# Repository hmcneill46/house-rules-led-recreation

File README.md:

# house-rules-led-recreation
Software attempt at recreating Rose Finn-Kelcey's House Rules

[Web App](https://hmcneill46.github.io/house-rules-led-recreation/)

The physical display project is documented in [hardware revision B2](hardware/revisions/B2/README.md), including editable KiCad files, firmware, printable case models, verification and prototype cost evidence. B2 uses the seven owned 5 × 7 LED modules on a hidden custom PCB, with ready-assembled controller and USB modules to reduce prototype cost.

The earlier hardware design is preserved at [hardware-a1-2026-10-29](https://github.com/hmcneill46/house-rules-led-recreation/tree/hardware-a1-2026-10-29). Read each revision's status and assembly guide before ordering or mixing files.

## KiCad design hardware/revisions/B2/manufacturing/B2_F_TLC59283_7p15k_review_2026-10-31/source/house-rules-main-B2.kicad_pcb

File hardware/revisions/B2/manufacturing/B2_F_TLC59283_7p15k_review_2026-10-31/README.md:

# House Rules B2 — MANUFACTURING REVIEW, NOT PRODUCTION APPROVAL

This package passed a fresh native KiCad10 DRC including warnings, exclusions,
unconnected items and schematic parity, after refilling/saving a staged copy.
The five ignored checks that KiCad10.0.7 uses by default are reported
explicitly; their pristine native evidence is included in reports/. UUID
exclusions, custom-rule ignores and other ignored-rule overrides are forbidden.
Its native audit checks82 references,55 factory parts,327 connected pins and the
84 LED holes against frozen A1 plus the owner-confirmed rigid module shifts
(175000nm per zero-based module index,12.875mm pitch). Individual pin patterns
and open0.90mm drill diameters stay unchanged. Separate owner-reported diode tests
verify the full12-terminal map and front orientation of ONE owned
LMD07057AUE-101B-02: part-number label on the left in the correct front view.
The other20 modules remain unverified. This does not establish powered-board
operation, actual soldered fit, USB current/compliance, brightness, thermal
performance or print fit. The owner evidence is included in reports/.
No upload, order or payment has been made by the exporter.

CURRENT DRIVER: U1..U4 = TLC59283RGER / C485815; R1..R4 =7.15k1%,
0603WAF7151T5E / C25980. Never use the historical TLC59282/6.8k BOM for
this revision. Copper, LED pitch and case geometry are preserved. Nominal
current is1.208*43.8/7.15=7.40006mA;400Hz/five phases/470us light remain.
BLANK HIGH also enables TLC59283 output precharge. Powered-off leakage and
rail transient behaviour are unspecified: both switched rails/QOD and the
clear/blank/control-low shutdown sequence remain necessary. Scope startup,
shutdown, reset/suspend and scanning; measure current, brightness uniformity,
ghosting and enclosed temperature. Static ERC/DRC cannot qualify those effects.
The owner has NOT yet completed the full case print/stock-module/plug trial.
Case fit and factory CAM/pin1 review remain pending before any order decision.

Board requirements: SIX copper layers,89.45 x17.3mm final outline,1.6mm FR4.
Layer order is F.Cu/In1.Cu/In2.Cu/In3.Cu/In4.Cu/B.Cu. In4 is GND-only. In2 is
primarily GND with one explicitly approved quiet CT_5V timing-capacitor bridge,
maximum12mm total; no other signal is allowed there. Its GND fill must remain
one connected outline. The final measured length is recorded in the audit.
In3 has signal copper including USB and GND fill; USB retains its unbroken
In4 ground reference. Confirm the actual standard dielectric
stack with the manufacturer. No controlled-impedance certification is claimed.

ALL0.30mm ordinary F-to-B plated through VIAS must be epoxy/resin FILLED and
COPPER CAPPED flat, including12 exposed-pad thermal vias (three per TLC driver)
and the selective0.45mm-pad escape vias. Most via pads are0.60mm; selected escape
pads are0.45mm, minimum annulus0.075mm. Tenting or solder plugging alone is not
equivalent to this fill/cap requirement. No blind/buried/laser vias are specified.

Actual Excellon PTH T1 =0.30mm VIA holes: FILL AND CAP ALL.
Actual Excellon PTH T2 =0.90mm LED mounting holes, exactly84: KEEP OPEN,
UNFILLED AND UNCAPPED. Never apply a blanket fill instruction to all PTH holes.
The actual drill counts and source/output hashes are in manifest.json and
reports/drill-statistics.json. There must be no other finished-board hole tools.
Both native geometry and actual Excellon holes are independently checked for
at least0.45mm via-to-LED-PTH hole-edge clearance and0.25mm via-to-via clearance,
including same-net pairs. These physical checks do not depend on copper DRC.

Narrow-board assembly may need REMOVABLE OUTSIDE RAILS and tooling chosen by the
assembler. Tooling/fiducial holes must be OUTSIDE the finished89.45x17.3mm outline,
on removable rails only. Do not add holes inside the main board or move/close the
84 LED holes. Rails must depanelise completely so the final PCB stays hidden
behind the LEDs. CAM must confirm fill/cap selection, open LED holes and final
outline tolerance before an order is approved.

Factory assembly:55 SMT components on BOTTOM ONLY. DS1..DS7 andJ1..J20 are
owner-fit modules/wire lands, excluded from every factory BOM/CPL. Their copper
and LED holes remain in Gerbers. Do not solder-fill the84 empty LED holes.
The owner supplies the XIAO RP2040 Plus and Adafruit4090 separately and wires
20 leads/40 wire-end joints; these stock modules/looms are not factory BOM parts.

ROTATION REVIEW IS REQUIRED. bom.csv uses common JLC-shaped headings; bom-review
adds exact quantities/identities. cpl-manufacturer-review.csv preserves KiCad's
native millimetre position export, same auxiliary origin as Gerbers/drill.
BOTTOM X IS NOT NEGATED. Native exported Y can be negative. No extra mirroring,
Y inversion or package-specific angle correction has been applied. Native angles
are NOT a guarantee of the manufacturer's tape/feeder/pin1 convention.
placement-review.csv adds native pad1 coordinates relative to the auxiliary
origin, using native board XY (distinct from exported CPL Y), BOTTOM side,
exact MPN/LCSC, native angle and uncorrected CPL rotation. Review
all asymmetric components in the assembler's placement preview, especially QFNs,
PMOS switches, load switches, ESD/BC chips and diode polarity. Obtain the factory's
concrete placement/process review before production. No silent substitutions.

fabrication/ contains six actual Gerber X2 copper layers, both masks/silks, outline,
metric Excellon PTH/NPTH, drill map and Gerber job metadata. Its ZIP contains
fabrication files only. assembly/ adds paste Gerbers and factory CSVs. reports/
contains native DRC, exact board audit and actual drill statistics. source/ retains
the exact refilled/saved board used for these outputs plus project/schematic/rules
and local footprint libraries. source/3d/ includes the bundled model assets.
Every model referenced by the actual staged PCB must resolve through
${KIPRJMOD}/3d/ inside this snapshot; installed/global model fallbacks, absolute
paths and escaping relative paths are rejected. reports/3d-model-portability.json
records each reference/hash and explicitly lists footprints lacking a 3D model.
Absent models are not a claim of absent physical components. The repository
also retains generators, mechanical design, firmware and earlier source history.
The source canonical PCB was not modified. manifest.json links all inputs and
outputs to SHA256 hashes; a later change requires a fresh audit/export/quote.

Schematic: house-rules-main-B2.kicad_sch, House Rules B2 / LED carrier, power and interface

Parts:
C1, C2, C3, C4, C15: 100n 50V X7R; C_0603_1608Metric; MPN CC0603KRX7R9BB104; LCSC C14663
C5, C6, C7, C14, C16: 1u 50V X5R; C_0603_1608Metric; MPN CL10A105KB8NNNC; LCSC C15849
C8: 4u7 16V X5R; C_0603_1608Metric; MPN CL10A475KO8NNNC; LCSC C19666
C9, C10, C13: 1n 50V X7R; C_0603_1608Metric; MPN CL10B102KB8NNNC; LCSC C1588
C11, C12: 10n 50V X7R; C_0603_1608Metric; MPN 0603B103K500NT; LCSC C57112
D1: SMF5.0A; D_SOD-123F; MPN SMF5.0A; LCSC C151296
DS1, DS2, DS3, DS4, DS5, DS6, DS7: LMD07057AUE-101B; MPN LMD07057AUE-101B
F1: 750mA PPTC; Fuse_1206_3216Metric; MPN SMD1206B075TF/16; LCSC C269118
J1: +5V; WirePad_B2; MPN +5V
J2, J14: GND; WirePad_B2; MPN GND
J3: +3V3; WirePad_B2; MPN +3V3
J4: SIN; WirePad_B2; MPN SIN
J5: SCLK; WirePad_B2; MPN SCLK
J6: LAT; WirePad_B2; MPN LAT
J7: BLANK; WirePad_B2; MPN BLANK
J8: DRIVER_EN; WirePad_B2; MPN DRIVER_EN
J9: CC1_ADC; WirePad_B2; MPN CC1_ADC
J10: CC2_ADC; WirePad_B2; MPN CC2_ADC
J11: USB_DM_HOST; WirePad_B2; MPN USB_DM_HOST
J12: USB_DP_HOST; WirePad_B2; MPN USB_DP_HOST
J13: VBUS; WirePad_B2; MPN VBUS
J15: CC1; WirePad_B2; MPN CC1
J16: CC2; WirePad_B2; MPN CC2
J17: USB_DM; WirePad_B2; MPN USB_DM
J18: USB_DP; WirePad_B2; MPN USB_DP
J19: BC_DET; WirePad_B2; MPN BC_DET
J20: BC_AL_N; WirePad_B2; MPN BC_AL_N
Q1, Q2, Q3, Q4, Q5: AO3401A; SOT-23; MPN AO3401A; LCSC C15127
R1, R2, R3, R4: 7k15 1%; R_0603_1608Metric; MPN 0603WAF7151T5E; LCSC C25980
R5, R6, R7, R8, R9, R15: 4k7 1%; R_0603_1608Metric; MPN 0603WAF4701T5E; LCSC C23162
R10, R11, R12, R13, R14, R21, R23: 10k 1%; R_0603_1608Metric; MPN 0603WAF1002T5E; LCSC C25804
R16: 100k 1%; R_0603_1608Metric; MPN 0603WAF1003T5E; LCSC C25803
R17, R18, R19, R20: 47k 1%; R_0603_1608Metric; MPN 0603WAF4702T5E; LCSC C25819
R22: 15k 1%; R_0603_1608Metric; MPN 0603WAF1502T5E; LCSC C22809
U1, U2, U3, U4: TLC59283RGER; RGE0024C; MPN TLC59283RGER; LCSC C485815
U5, U6, U8: TPS22918DBVR; SOT-23-6; MPN TPS22918DBVR; LCSC C131941
U7: TPD4E05U06DQAR; USON-10_2.5x1.0mm_P0.5mm; MPN TPD4E05U06DQAR; LCSC C138714
U9: BQ24392RSER; Texas_UQFN-10_1.5x2mm_P0.5mm; MPN BQ24392RSER; LCSC C128408

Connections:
+3V3: C5.1, J3.1, R23.2, U5.1 (VIN), U9.5 (GOOD_BAT)
+5V: C6.1, C15.1, C16.1, J1.1, U6.1 (VIN), U8.5 (QOD), U8.6 (VOUT), U9.9 (VBUS)
BC_AL_N: J20.1, R23.1, U9.4 (CHG_AL_N)
BC_DET: J19.1, R21.2, R22.1
BC_DET_5V: R21.1, U9.10 (CHG_DET)
BLANK: J7.1, R15.1, U1.18 (BLANK), U2.18 (BLANK), U3.18 (BLANK), U4.18 (BLANK)
CC1: J15.1, R17.1, U7.4, U7.7
CC1_ADC: C11.1, J9.1, R17.2, R18.1
CC2: J16.1, R19.1, U7.5, U7.6
CC2_ADC: C12.1, J10.1, R19.2, R20.1
COL1_A: DS1.1, DS2.1, DS3.1, DS4.1, DS5.1, DS6.1, DS7.1, Q1.3 (D), R10.1
COL1_GATE: Q1.1 (G), R5.1, U4.9 (OUT7)
COL2_A: DS1.3, DS2.3, DS3.3, DS4.3, DS5.3, DS6.3, DS7.3, Q2.3 (D), R11.1
COL2_GATE: Q2.1 (G), R6.1, U4.10 (OUT8)
COL3_A: DS1.10, DS2.10, DS3.10, DS4.10, DS5.10, DS6.10, DS7.10, Q3.3 (D), R12.1
COL3_GATE: Q3.1 (G), R7.1, U4.11 (OUT9)
COL4_A: DS1.7, DS2.7, DS3.7, DS4.7, DS5.7, DS6.7, DS7.7, Q4.3 (D), R13.1
COL4_GATE: Q4.1 (G), R8.1, U4.12 (OUT10)
COL5_A: DS1.8, DS2.8, DS3.8, DS4.8, DS5.8, DS6.8, DS7.8, Q5.3 (D), R14.1
COL5_GATE: Q5.1 (G), R9.1, U4.13 (OUT11)
CT_3V3: C9.1, U5.4 (CT)
CT_5V: C10.1, U6.4 (CT)
CT_INPUT: C13.1, U8.4 (CT)
D1_ROW1_K: DS1.12, U1.2 (OUT0)
D1_ROW2_K: DS1.11, U1.3 (OUT1)
D1_ROW3_K: DS1.2, U1.4 (OUT2)
D1_ROW4_K: DS1.9, U1.5 (OUT3)
D1_ROW5_K: DS1.4, U1.6 (OUT4)
D1_ROW6_K: DS1.5, U1.7 (OUT5)
D1_ROW7_K: DS1.6, U1.8 (OUT6)
D1_ROW8_K: DS2.12, U1.9 (OUT7)
D1_ROW9_K: DS2.11, U1.10 (OUT8)
D1_ROW10_K: DS2.2, U1.11 (OUT9)
D1_ROW11_K: DS2.9, U1.12 (OUT10)
D1_ROW12_K: DS2.4, U1.13 (OUT11)
D1_ROW13_K: DS2.5, U1.14 (OUT12)
D1_ROW14_K: DS2.6, U1.15 (OUT13)
D2_ROW1_K: DS3.12, U2.2 (OUT0)
D2_ROW2_K: DS3.11, U2.3 (OUT1)
D2_ROW3_K: DS3.2, U2.4 (OUT2)
D2_ROW4_K: DS3.9, U2.5 (OUT3)
D2_ROW5_K: DS3.4, U2.6 (OUT4)
D2_ROW6_K: DS3.5, U2.7 (OUT5)
D2_ROW7_K: DS3.6, U2.8 (OUT6)
D2_ROW8_K: DS4.12, U2.9 (OUT7)
D2_ROW9_K: DS4.11, U2.10 (OUT8)
D2_ROW10_K: DS4.2, U2.11 (OUT9)
D2_ROW11_K: DS4.9, U2.12 (OUT10)
D2_ROW12_K: DS4.4, U2.13 (OUT11)
D2_ROW13_K: DS4.5, U2.14 (OUT12)
D2_ROW14_K: DS4.6, U2.15 (OUT13)
D3_ROW1_K: DS5.12, U3.2 (OUT0)
D3_ROW2_K: DS5.11, U3.3 (OUT1)
D3_ROW3_K: DS5.2, U3.4 (OUT2)
D3_ROW4_K: DS5.9, U3.5 (OUT3)
D3_ROW5_K: DS5.4, U3.6 (OUT4)
D3_ROW6_K: DS5.5, U3.7 (OUT5)
D3_ROW7_K: DS5.6, U3.8 (OUT6)
D3_ROW8_K: DS6.12, U3.9 (OUT7)
D3_ROW9_K: DS6.11, U3.10 (OUT8)
D3_ROW10_K: DS6.2, U3.11 (OUT9)
D3_ROW11_K: DS6.9, U3.12 (OUT10)
D3_ROW12_K: DS6.4, U3.13 (OUT11)
D3_ROW13_K: DS6.5, U3.14 (OUT12)
D3_ROW14_K: DS6.6, U3.15 (OUT13)
D4_ROW1_K: DS7.12, U4.2 (OUT0)
D4_ROW2_K: DS7.11, U4.3 (OUT1)
D4_ROW3_K: DS7.2, U4.4 (OUT2)
D4_ROW4_K: DS7.9, U4.5 (OUT3)
D4_ROW5_K: DS7.4, U4.6 (OUT4)
D4_ROW6_K: DS7.5, U4.7 (OUT5)
D4_ROW7_K: DS7.6, U4.8 (OUT6)
DRIVER_EN: J8.1, R16.1, U5.3 (ON), U6.3 (ON)
FUSED_VBUS: C14.1, F1.2, U8.1 (VIN), U8.3 (ON)
GND: C1.2, C2.2, C3.2, C4.2, C5.2, C6.2, C7.2, C8.2, C9.2, C10.2, C11.2, C12.2, C13.2, C14.2, C15.2, C16.2, D1.2, J2.1, J14.1, R1.2, R2.2, R3.2, R4.2, R10.2, R11.2, R12.2, R13.2, R14.2, R16.2, R18.2, R20.2, R22.2, U1.22 (GND), U1.25 (EP_GND), U2.22 (GND), U2.25 (EP_GND), U3.22 (GND), U3.25 (EP_GND), U4.22 (GND), U4.25 (EP_GND), U5.2 (GND), U6.2 (GND), U7.3, U7.8, U8.2 (GND), U9.6 (GND)
IREF1: R1.1, U1.20 (IREF)
IREF2: R2.1, U2.20 (IREF)
IREF3: R3.1, U3.20 (IREF)
IREF4: R4.1, U4.20 (IREF)
LAT: J6.1, U1.1 (LAT), U2.1 (LAT), U3.1 (LAT), U4.1 (LAT)
SCLK: J5.1, U1.24 (SCLK), U2.24 (SCLK), U3.24 (SCLK), U4.24 (SCLK)
SERIAL_1_2: U1.19 (SOUT), U2.23 (SIN)
SERIAL_2_3: U2.19 (SOUT), U3.23 (SIN)
SERIAL_3_4: U3.19 (SOUT), U4.23 (SIN)
SIN: J4.1, U1.23 (SIN)
SW_3V3: C1.1, C2.1, C3.1, C4.1, C7.1, R15.2, U1.21 (VCC), U2.21 (VCC), U3.21 (VCC), U4.21 (VCC), U5.5 (QOD), U5.6 (VOUT)
USB_DM: J17.1, U7.1, U7.10, U9.8 (DM_CON)
USB_DM_HOST: J11.1, U9.2 (DM_HOST)
USB_DP: J18.1, U7.2, U7.9, U9.7 (DP_CON)
USB_DP_HOST: J12.1, U9.3 (DP_HOST)
VBUS: D1.1, F1.1, J13.1
VLED_5V: C8.1, Q1.2 (S), Q2.2 (S), Q3.2 (S), Q4.2 (S), Q5.2 (S), R5.2, R6.2, R7.2, R8.2, R9.2, U6.5 (QOD), U6.6 (VOUT)

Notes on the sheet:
BANK1 / DS1 + DS2
BANK2 / DS3 + DS4
BANK3 / DS5 + DS6
BANK4 / DS7 and gate sinks / USB INPUT SOFT START
COLUMN1..3 / gate pullups and anode discharge
COLUMN4..5 / gate pullups and anode discharge
RAIL SWITCHES / common EN / quick discharge
USB / CC current sensing and ESD
BC1.2 / automatic USB switch / GOOD_BAT uses always3V3
MCU WIRES J1..J10 / external XIAO RP2040 Plus
MCU DATA / BC STATUS + USB BREAKOUT WIRES / do not power both USB sockets
Named labels connect matching nodes. Every package pin is explicit; crosses mark intentional no-connects. Owner-supplied LEDs and wire pads are excluded from factory assembly.
TLC59283RGER + IREF=7.15k: 7.40006mA nominal. U4 OUT7..11 sink PMOS gates, exactly one selected column. BLANK HIGH disables sinks and enables precharge.
400Hz frame / 5x500us phases / >=30us BLANK before next phase / <=470us full on. LAT LOW while shifting, pulse HIGH then LOW while blanked.
USB-C 5V only, no PD. Adafruit4090 supplies separate5.1k Rd resistors; no duplicate Rd on this board. CC divider loading checked against tolerance.
Both TPS22918 switches default OFF. BLANK pullup uses SW_3V3. Park serial controls LOW and BLANK high-Z before disabling rails to prevent backfeed.
TPD4E05U06 opposite NC pads are joined by external copper to corresponding DC nets. Do not treat the IC as internally flow-through.
BQ24392 isolates raw USB_DP/DM from USB_DP_HOST/DM_HOST. GOOD_BAT always3V3; BC full grant requires DET HIGH and AL_N LOW; host suspend always overrides.
One owned LED diode-verified; check other20. Full case print pending. Precharge/rail transients/current/inrush/suspend, 30us settling and temperature need bench tests. In2: CT_5V<=12mm only; In4: pure GND.

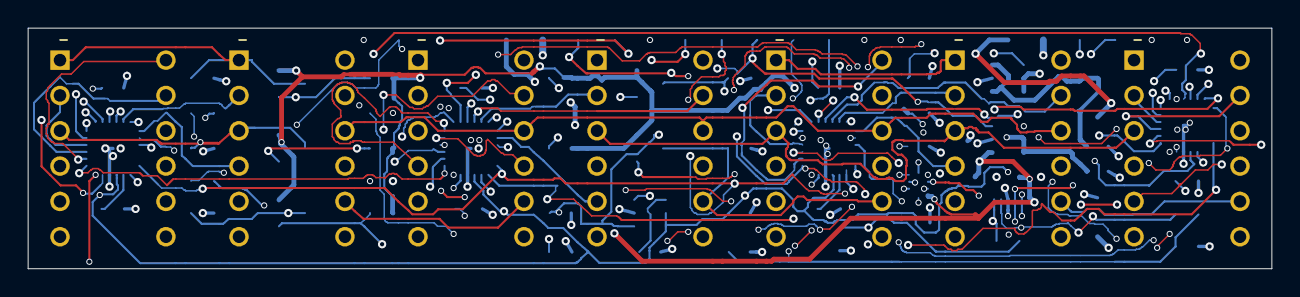
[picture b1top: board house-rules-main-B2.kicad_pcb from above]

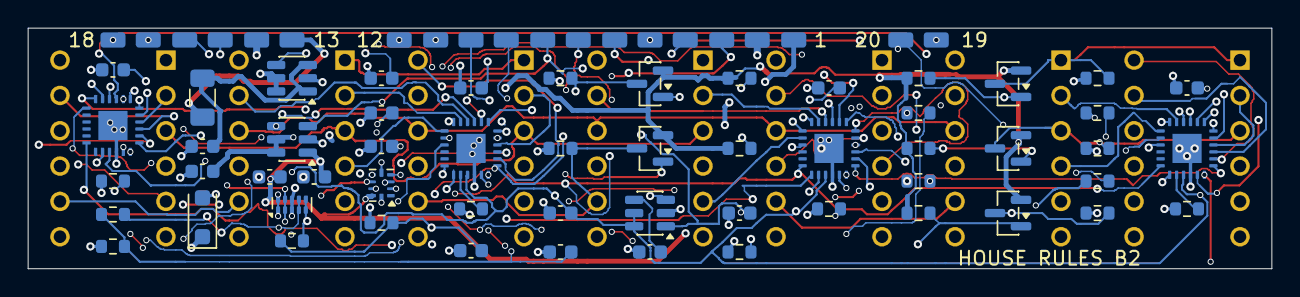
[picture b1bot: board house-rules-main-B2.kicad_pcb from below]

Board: 6 copper layers, 89.4 x 17.3 mm, 82 parts (75 on the bottom side), 92 nets.

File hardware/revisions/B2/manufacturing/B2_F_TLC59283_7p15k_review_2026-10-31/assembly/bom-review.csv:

MPN,LCSC,Qty,Designators,Value,Footprint
0603B103K500NT,C57112,2,"C11,C12",10n 50V X7R,Capacitor_SMD:C_0603_1608Metric
0603WAF1002T5E,C25804,7,"R10,R11,R12,R13,R14,R21,R23",10k 1%,Resistor_SMD:R_0603_1608Metric
0603WAF1003T5E,C25803,1,R16,100k 1%,Resistor_SMD:R_0603_1608Metric
0603WAF1502T5E,C22809,1,R22,15k 1%,Resistor_SMD:R_0603_1608Metric
0603WAF4701T5E,C23162,6,"R5,R6,R7,R8,R9,R15",4k7 1%,Resistor_SMD:R_0603_1608Metric
0603WAF4702T5E,C25819,4,"R17,R18,R19,R20",47k 1%,Resistor_SMD:R_0603_1608Metric
0603WAF7151T5E,C25980,4,"R1,R2,R3,R4",7k15 1%,Resistor_SMD:R_0603_1608Metric
AO3401A,C15127,5,"Q1,Q2,Q3,Q4,Q5",AO3401A,Package_TO_SOT_SMD:SOT-23
BQ24392RSER,C128408,1,U9,BQ24392RSER,Package_DFN_QFN:Texas_UQFN-10_1.5x2mm_P0.5mm
CC0603KRX7R9BB104,C14663,5,"C1,C2,C3,C4,C15",100n 50V X7R,Capacitor_SMD:C_0603_1608Metric
CL10A105KB8NNNC,C15849,5,"C5,C6,C7,C14,C16",1u 50V X5R,Capacitor_SMD:C_0603_1608Metric
CL10A475KO8NNNC,C19666,1,C8,4u7 16V X5R,Capacitor_SMD:C_0603_1608Metric
CL10B102KB8NNNC,C1588,3,"C9,C10,C13",1n 50V X7R,Capacitor_SMD:C_0603_1608Metric
SMD1206B075TF/16,C269118,1,F1,750mA PPTC,Fuse:Fuse_1206_3216Metric
SMF5.0A,C151296,1,D1,SMF5.0A,Diode_SMD:D_SOD-123F
TLC59283RGER,C485815,4,"U1,U2,U3,U4",TLC59283RGER,TI:RGE0024C
TPD4E05U06DQAR,C138714,1,U7,TPD4E05U06DQAR,Package_SON:USON-10_2.5x1.0mm_P0.5mm
TPS22918DBVR,C131941,3,"U5,U6,U8",TPS22918DBVR,Package_TO_SOT_SMD:SOT-23-6

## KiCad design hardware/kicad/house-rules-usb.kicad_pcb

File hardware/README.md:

# Physical House Rules — prototype A1

**Historical A1 design.** The current build is [revision B2](revisions/B2/README.md), updated on 31 October to the owner's confirmed 12.875 mm module pitch and 89.45 mm PCB width. The earlier 12.70 mm fit assumption and files below are superseded for new builds. They remain here as design history.

A complete editable electronics design for seven owner-supplied Wenrun LMD07057AUE-101B displays, arranged as a **35 × 7, 245-dot** screen. Designed 29 October 2026. This is a **prototype awaiting physical validation**, with fabrication and assembly files for review. No boards have been ordered or tested. Start with [the illustrated summary](design-summary.html).

## What was designed

| Item | Design |
| --- | --- |
| Display arrangement | Seven upright modules, 12.70 mm centre spacing; user reports seven-module printed-fixture fit passed |
| Main PCB | 88.4 × 17.3 × 1.6 mm, six copper layers |
| USB carrier | 16.0 × 16.8 × 1.0 mm, four copper layers, behind right end |
| Drivers | Four IS31FL3729-QFLS4-TR, addressing 2 + 2 + 2 + 1 modules |
| Controller | STM32G0B1KBU6, 128 KB flash, native USB and factory DFU |
| Factory assembly | 37 main-board SMD placements on B; seven carrier placements on F |
| Owner assembly | Seven LED modules: 84 through-hole joints per unit; plug-in six-wire harness |
| Power | USB 5 V only; both A-to-C and C-to-C cables |
| Enclosure concept | 93.6 × 22.6 × 24 mm, printable shell and removable rear carrier cradle |

The PCB is inset 0.25 mm from the **nominal** 88.9 × 17.8 mm seven-module envelope. On 29 October 2026 the owner reported that the printed pin-fit plate worked and all seven LED modules fitted very nicely. The plate shares the main PCB's 88.4 × 17.3 mm outline and 84 pin centres. Its 1.0 mm thickness and nominal 1.0 mm holes differ from the main PCB's 1.6 mm thickness and 0.9 mm finished holes. This confirms the reported group's mechanical arrangement, while electrical orientation, actual PCB hole tolerances and the other two groups remain separate checks. See [the recorded user fit result](reports/user-fit-confirmation-2026-10-29.json).

The USB carrier solves a physical conflict: the selected USB socket will not fit directly between the LED solder leads. It remains within the display's projected outline and connects through a short keyed JST-SH six-way harness, with a vertical header on the main board to clear the LED lead stubs. The bottom-right socket sits approximately **1.825 mm recessed** behind the concept case's outer wall, with a 14 × 6.5 mm plug well. A cable plug protrudes. The case is an editable fit concept; verify the chosen plug and actual assembly before printing a final shell.

## Where to look

- [Main KiCad project](kicad/house-rules-main.kicad_pro), [main PCB](kicad/house-rules-main.kicad_pcb), [schematic](kicad/house-rules-main.kicad_sch).
- [USB KiCad project](kicad/house-rules-usb.kicad_pro), [carrier PCB](kicad/house-rules-usb.kicad_pcb), [schematic](kicad/house-rules-usb.kicad_sch).
- [Native CAD renders](render/), including front with LEDs, bare front, component rear and carrier views.
- Manufacturing review output: `manufacturing/A1_review/`, generated after final CAD checks. It contains separate Gerber/drill archives, exact-part BOM and placement files for each board. The illustrated summary links it once exported; it is a review package, not an instruction to order immediately.
- [Offline pin-level simulator](simulation/matrix-emulator.html), [model scope](simulation/README.md).
- [Compiled firmware and programming guide](firmware/README.md), [BIN](firmware/compiled/HouseRules.ino.bin), [ELF](firmware/compiled/HouseRules.ino.elf).
- [1:1 pin-fit template](mechanical/pin-fit-template.svg), [soldering alignment tray](mechanical/README.md), [case and assembly stack](mechanical/enclosure-notes.md).
- [Assembly and test instructions](assembly-and-test.md), [verification reports](reports/).

## Electronics and brightness

These are raw LED matrices, with no controller or current limiting inside. The [Wenrun datasheet](https://cdn.shopify.com/s/files/1/0695/1347/8453/files/LMD07057AUE.pdf) specifies column anodes 1, 3, 10, 7, 8 (left to right) and row cathodes 12, 11, 2, 9, 4, 5, 6 (top to bottom). The custom footprint numbers the front-view left strip 1–6 downward and the right strip 12–7 downward. A physical single-pixel check is still required: the photos identify a -101B-Q2 suffix whose meaning is not established. Never connect a module directly across 5 V.

Each driver selects five shared anode columns and supplies independent current sinks to each module's seven rows. The paired modules share anodes only; their cathodes remain independent. Addresses are 0x34–0x37. Four 47 kohm, 1% ISET resistors limit nominal full-scale dot current to approximately **7.25 mA peak**, below the LED's 20 mA continuous absolute maximum. The 80 mA pulse rating is conditional on duty ≤1/10 and is **not applicable** to the selected five-phase scan. No separate resistor is needed for every dot because the drivers regulate current.

The calculated all-on LED load is approximately **342 mA average**, before MCU and driver overhead. The default dim mode uses approximately 43 mA average LED current. These are nominal calculations, not measured input current or guaranteed brightness. Compare brightness and timing with the reference and measure full-on temperature/current before considering any increase. Driver register details and source references are in [the functional model](simulation/README.md); local manufacturer PDFs are in [reference/](reference/).

The six-layer main board reserves In1 for GND and In4 for +5 V; F/In2/In3/B carry signals. The USB data pair follows the front copper's upper margin, with the adjacent GND layer providing its reference. Default copper clearance is 0.15 mm. A documented 0.10 mm via-to-pad rule applies only inside each LED driver courtyard, enabling filled/capped QFN fanout; via-to-track and via-to-via spacing retain the default. All vias are intended as ordinary full-stack through vias, with minimum 0.4 mm copper / 0.2 mm drill. There is no blind-via or HDI requirement. The design does not claim controlled 90-ohm impedance or USB certification; the short harness and entire USB path require hardware tests.

## USB and programming

Separate 5.1 kohm CC resistors make the board a 5 V USB-C sink in either plug orientation. No high-voltage Power Delivery negotiation is needed. The input has a resettable fuse, a 5 V TVS and data/CC ESD protection. Independent 47k/47k dividers let the MCU conservatively detect Type-C current advertisements without violating CC termination or ADC input-impedance limits.

Firmware starts with drivers disabled, performs source qualification, and uses full brightness only after a configured 500 mA USB connection, a positively identified BC1.2 charging port, or a conservative sufficient Type-C current indication. Unknown/default-current sources run dim; host suspend blanks and enters a low-power path. Inrush, total input/suspend current, BC1.2 detection and wake still require bench measurements. A fuse does not grant permission to draw current.

Use a **USB data cable** and STM32CubeProgrammer to load the factory USB DFU bootloader. A virgin blank MCU normally enters ROM automatically. After first programming, set and verify the documented G0B1 boot option bytes so holding BOOT while resetting re-enters DFU. Five SWD recovery pads remain accessible with the rear cover removed. BOOT shares PA14/SWCLK on this exact part. Follow [the exact programming steps](firmware/README.md); the running USB serial interface is not itself a flashing bootloader.

## Software checks and their limits

Native KiCad ERC, schematic-netlist comparison and PCB DRC/parity reports are saved in `reports/`. Check their current timestamps and counts; the illustrated summary reads the reports rather than assuming success. ERC/DRC establish represented connectivity and geometric rules, not physical LED identification, analogue behaviour or manufacturing yield.

The offline model reconstructs the display by traversing independently defined LED diode terminals and the actual module-to-driver connections. All 245 walking pixels and the artwork's 22,248 distinct windows were checked. Twenty-six host tests pass, including deliberate row/polarity/shared-cathode faults; see the timestamped [software verification record](reports/software-verification.json). A separately compiled C++ playback test compares **60,000 frames and two complete traversals** with the original recreation. The compiled ARM image occupies 66,108 bytes flash and 4,560 bytes static RAM. Its USB descriptor and critical startup/power hooks were inspected in the ELF. These checks do not execute the MCU or establish physical USB compliance.

## Manufacture and minimise repeat costs

Quote **three main boards and three carriers**, with the small components assembled and the 21 existing modules retained locally. Also compare a minimum pilot assembly quantity before committing all three. Fit and prove one unit before soldering the remaining 14 displays; a single assembly batch may avoid paying two sets of setup and UK shipping again. Use the full-size paper template and soldering jig first to reduce mechanical risk.

First supplier to quote is [JLCPCB Economic PCBA](https://jlcpcb.com/capabilities/pcb-assembly-capabilities): its published capabilities support these board dimensions, single-side assembly, 0.4 mm QFN pitch, 0402 parts and 2/4/6-layer boards. Main assembly is on B; carrier assembly is on F. The main BOOT switch has a 2.2 kohm series resistor so it can safely share PA14 with the SWD clock. Request green FR-4, 1 oz copper, standard six-layer 1.6 mm main stack and four-layer 1.0 mm carrier stack. Have the factory review QFN stencil/thermal vias and choose filled/capped treatment for exposed-pad vias; do not assume mask tenting will seal them. Confirm 0.2 mm drill/0.4 mm via pricing and exact part stock before paying. The manufacturer must check placement rotations and polarity in its assembly viewer.

[PCBWay assembly](https://www.pcbway.com/pcb-assembly.html) is a useful competing total-delivered quote. Bare boards alone are poor value if the tiny QFNs then need a separate assembler. No live project quote has been obtained; an earlier rough £40–90 allowance predated the final two-board, six-layer design and must not be treated as a price. Compare fabrication, two assembly setups, component/feeder fees, short harnesses, shipping and UK VAT together. The package contains exact MPN/LCSC fields and a sourcing review; stock snapshots are not reservations. Nothing has been purchased or uploaded to a manufacturer.

Before order: verify seven-module fit and pin orientation, review the Gerbers and assembly rotations, obtain the actual quote, and agree the thermal-via/stencil process. After delivery: inspect and test the empty electronics, program via USB, fit one LED and run diagnostics, then finish the first unit and measure it. Only after that should the other units be populated. A PCB electrical test cannot prove the animation or LED polarity.

## Tools and reproducibility

KiCad 10.0.7, Freerouting 2.5.0 and pinned Arduino tooling were installed locally. KiCad provides the editable schematic/PCB, native rule checks, manufacturing exports and faithful 3D images. [atopile](https://github.com/atopile/atopile) and [tscircuit](https://tscircuit.com/) are viable code-first tools; native KiCad was selected here for the custom footprint, tight mechanical layout and review/export workflow. Python-generated circuit data retains a code-readable source alongside the native files. No matching PCB MCP plugin was found in the available directory; no unofficial server was required.

`tools/circuit_spec.py` is the electrical/placement specification. `build_schematics.py --verify` rebuilds schematics and verifies their nets. **`build_pcbs.py` recreates placement and discards routing**; do not run it over a final routed board casually. Recorded `.dsn`/`.ses` files are routing intermediates, and the final native `.kicad_pcb` files include manual finishing work. `finalize_pcbs.py --metadata-only` refreshes fields without importing an old session. Preserve the final native boards as the deliverables. See [tool versions](design/tooling.txt) and [third-party library notices](kicad/third-party/README.md).

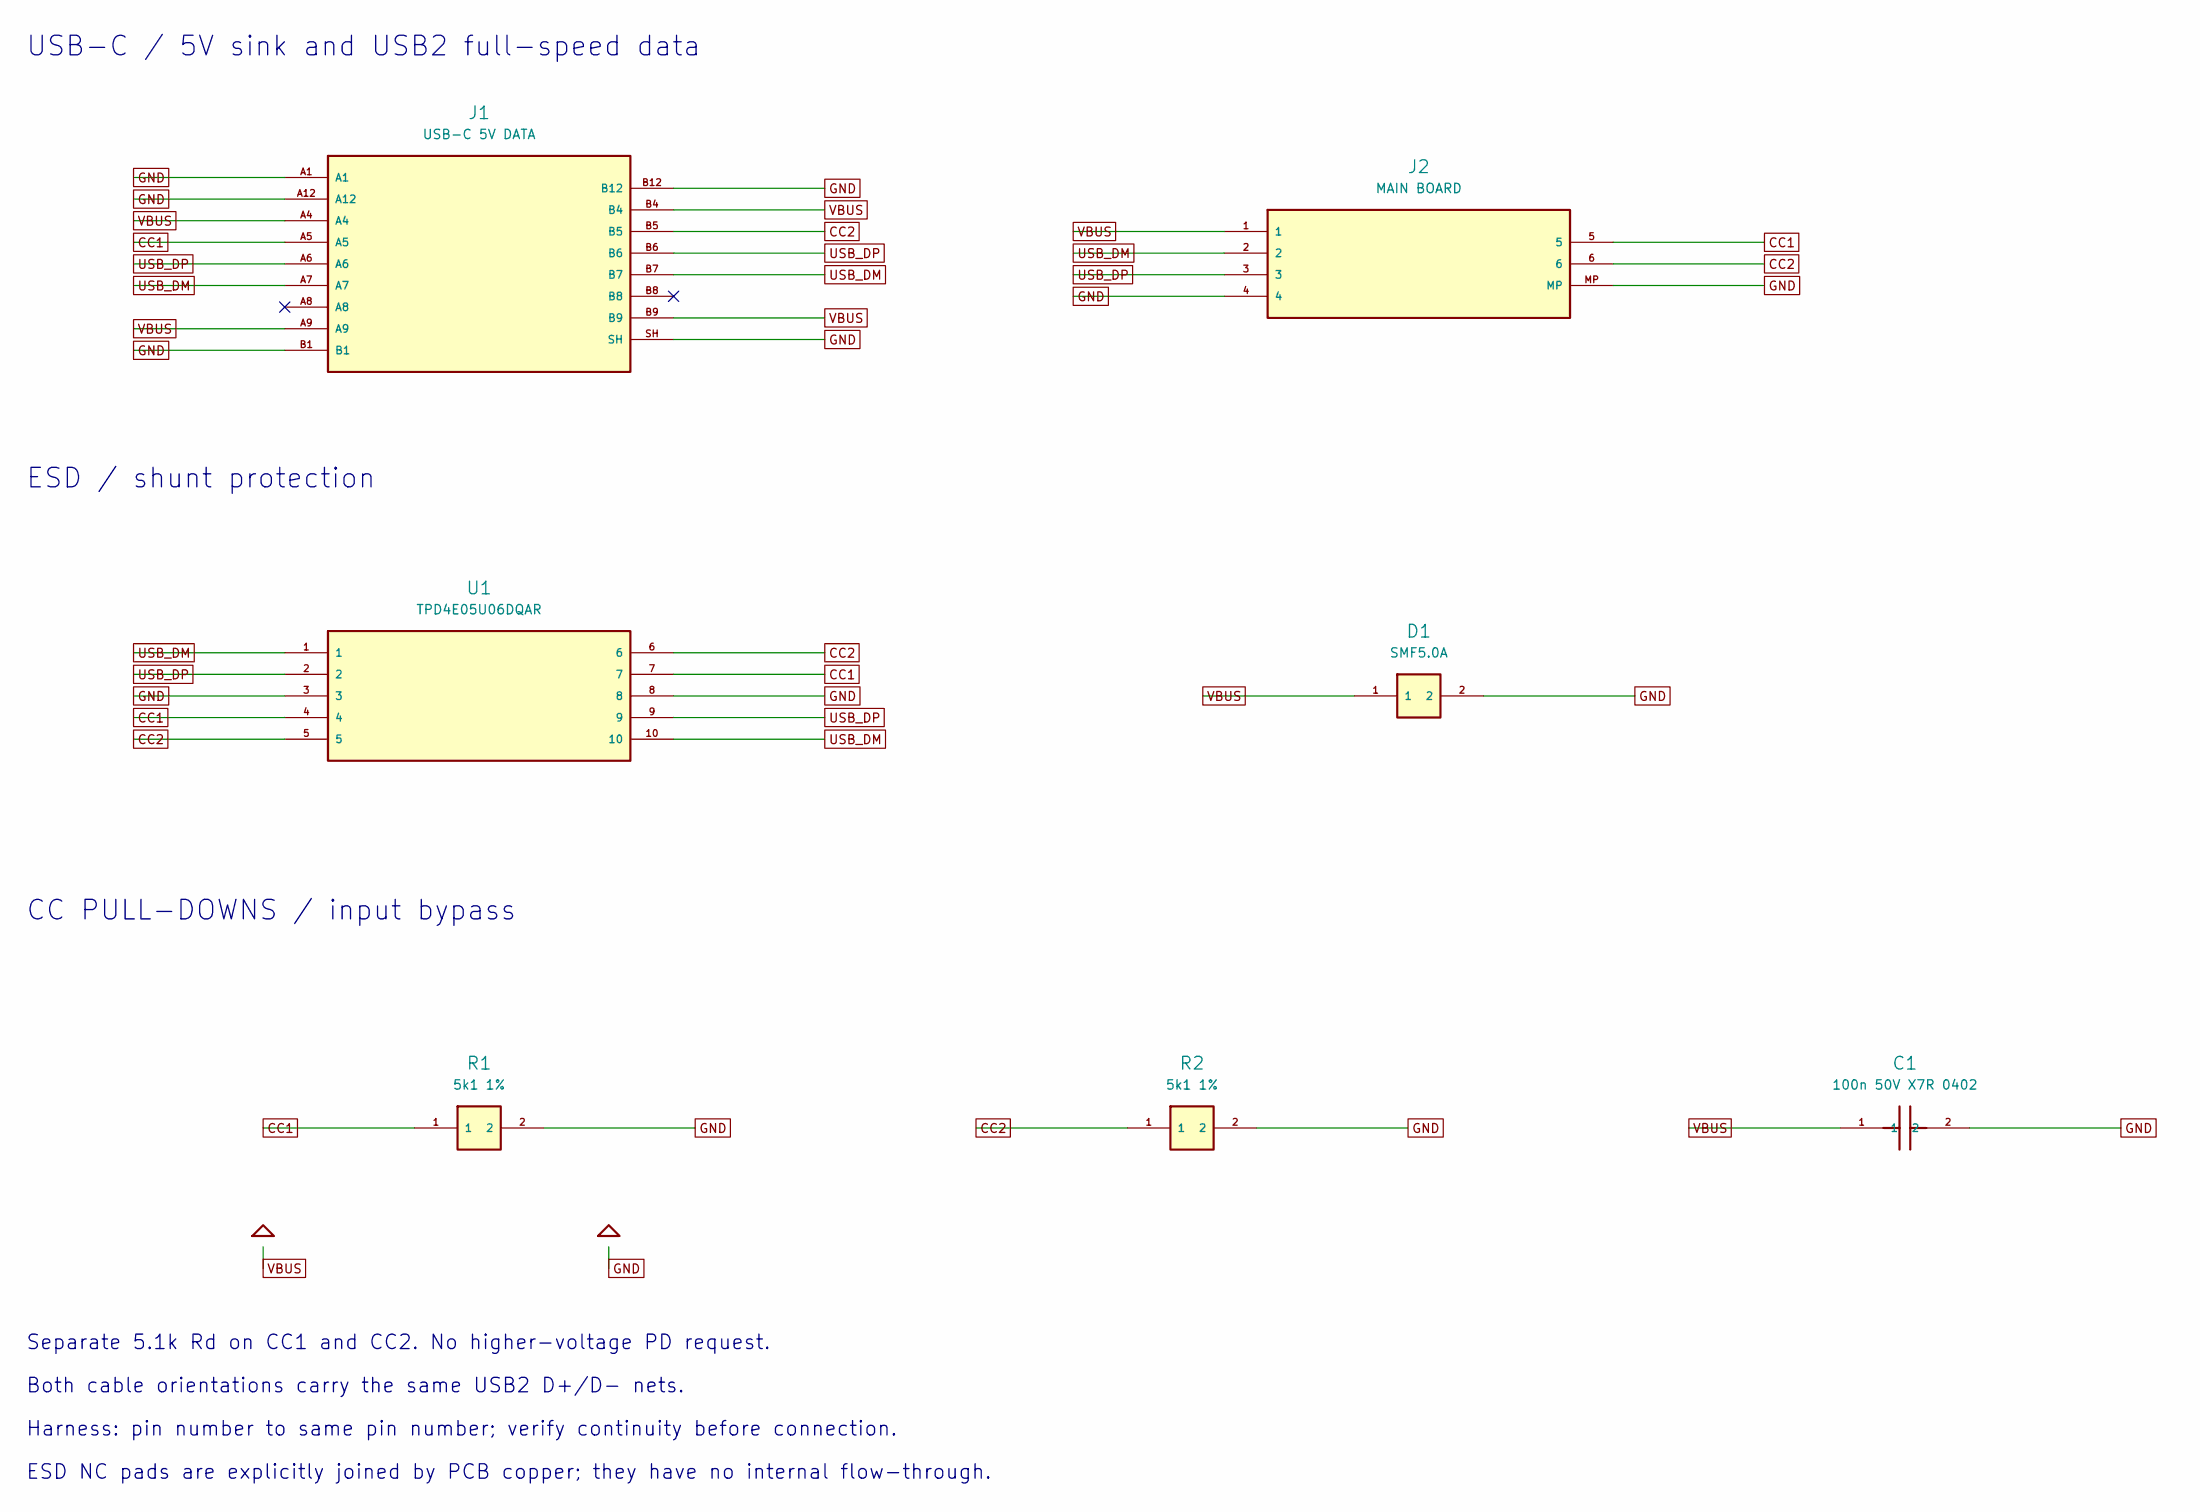
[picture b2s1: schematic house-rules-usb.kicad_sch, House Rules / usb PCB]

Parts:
C1: 100n 50V X7R 0402; C_0402_1005Metric; MPN CL05B104KB54PNC; LCSC C307331
D1: SMF5.0A; D_SOD-123F; MPN SMF5.0A; LCSC C151296
J1: USB-C 5V DATA; USB_C_Receptacle_GCT_USB4105-xx-A_16P_TopMnt_Horizontal; MPN USB4105-GF-A; LCSC C3020560
J2: MAIN BOARD; JST_SH_SM06B-SRSS-TB_1x06-1MP_P1.00mm_Horizontal; MPN SM06B-SRSS-TB(LF)(SN); LCSC C160405
R1, R2: 5k1 1%; R_0603_1608Metric; MPN 0603WAF5101T5E; LCSC C23186
U1: TPD4E05U06DQAR; USON-10_2.5x1.0mm_P0.5mm; MPN TPD4E05U06DQAR; LCSC C138714

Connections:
CC1: J1.A5, J2.5, R1.1, U1.4, U1.7
CC2: J1.B5, J2.6, R2.1, U1.5, U1.6
GND: C1.2, D1.2, J1.A1, J1.A12, J1.B1, J1.B12, J1.SH, J2.4, J2.MP, R1.2, R2.2, U1.3, U1.8
USB_DM: J1.A7, J1.B7, J2.2, U1.1, U1.10
USB_DP: J1.A6, J1.B6, J2.3, U1.2, U1.9
VBUS: C1.1, D1.1, J1.A4, J1.A9, J1.B4, J1.B9, J2.1

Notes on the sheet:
USB-C / 5V sink and USB2 full-speed data
ESD / shunt protection
CC PULL-DOWNS / input bypass
Separate 5.1k Rd on CC1 and CC2. No higher-voltage PD request.
Both cable orientations carry the same USB2 D+/D- nets.
Harness: pin number to same pin number; verify continuity before connection.
ESD NC pads are explicitly joined by PCB copper; they have no internal flow-through.

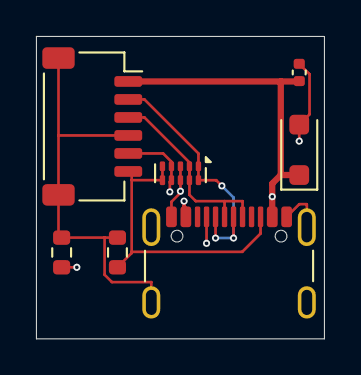
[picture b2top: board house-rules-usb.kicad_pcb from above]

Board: 4 copper layers, 16.0 x 16.8 mm, 7 parts (0 on the bottom side), 6 nets.

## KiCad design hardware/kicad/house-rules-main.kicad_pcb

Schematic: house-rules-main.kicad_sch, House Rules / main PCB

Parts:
C1, C3, C5, C7, C11, C12: 100n 50V X7R; C_0603_1608Metric; MPN CC0603KRX7R9BB104; LCSC C14663
C2, C4, C6, C8, C9, C13: 1u 16V X7R; C_0603_1608Metric; MPN 0603B105K160CT; LCSC C108463
C10: 2u2 10V X7R; C_0603_1608Metric; MPN 0603ZC225KAT2A; LCSC C2179699
DS1, DS2, DS3, DS4, DS5, DS6, DS7: LMD07057AUE-101B; MPN LMD07057AUE-101B
F1: 750mA PPTC; Fuse_1206_3216Metric; MPN SMD1206B075TF/16; LCSC C269118
J1: USB CARRIER; JST_SH_BM06B-SRSS-TB_1x06-1MP_P1.00mm_Vertical; MPN BM06B-SRSS-TB(LF)(SN); LCSC C160392
R1, R2, R3, R4, R10, R11, R12, R13: 47k 1%; R_0603_1608Metric; MPN 0603WAF4702T5E; LCSC C25819
R5, R6, R14: 2k2 1%; R_0603_1608Metric; MPN 0603WAF2201T5E; LCSC C4190
R7: 100k 1%; R_0603_1608Metric; MPN 0603WAF1003T5E; LCSC C25803
R8, R9: 10k 1%; R_0603_1608Metric; MPN 0603WAF1002T5E; LCSC C25804
SW1: BOOT; SW_SPST_EVQP7A; MPN EVQP7A01P; LCSC C79167
SW2: RESET; SW_SPST_EVQP7A; MPN EVQP7A01P; LCSC C79167
TP1: GND; TestPoint_Pad_D1.0mm; MPN GND
TP2: 3V3; TestPoint_Pad_D1.0mm; MPN 3V3
TP3: SWDIO; TestPoint_Pad_D1.0mm; MPN SWDIO
TP4: SWCLK; TestPoint_Pad_D1.0mm; MPN SWCLK
TP5: NRST; TestPoint_Pad_D1.0mm; MPN NRST
TP6: 5V; TestPoint_Pad_D1.0mm; MPN 5V
U1, U2, U3, U4: IS31FL3729-QFLS4-TR; QFN-32-1EP_4x4mm_P0.4mm_EP2.65x2.65mm; MPN IS31FL3729-QFLS4-TR; LCSC C2940549
U5: STM32G0B1KBU6; QFN-32-1EP_5x5mm_P0.5mm_EP3.45x3.45mm; MPN STM32G0B1KBU6; LCSC C5159549
U6: TLV75533PDBVR; SOT-23-5; MPN TLV75533PDBVR; LCSC C404027

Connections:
+3V3: C10.1, C11.1, R5.1, R6.1, R8.2, SW1.2, TP2.1, U5.4 (VDD_VDDA), U6.5 (OUT)
+5V: C1.1, C2.1, C3.1, C4.1, C5.1, C6.1, C7.1, C8.1, C9.1, C13.1, F1.2, TP6.1, U1.23 (VCC), U2.23 (VCC), U3.23 (VCC), U4.23 (VCC), U4.28 (AD), U6.1 (IN), U6.3 (EN)
BOOT_BUTTON: R14.1, SW1.1
BOOT_SWCLK: R9.1, R14.2, TP4.1, U5.25 (PA14_BOOT0_SWCLK)
CC1: J1.5, R10.1
CC1_ADC: R10.2, R11.1, U5.7 (PA0_ADC_CC1)
CC2: J1.6, R12.1
CC2_ADC: R12.2, R13.1, U5.8 (PA1_ADC_CC2)
D1_CS1: DS1.12 (ROW1_K), U1.30 (CS1)
D1_CS2: DS1.11 (ROW2_K), U1.31 (CS2)
D1_CS3: DS1.2 (ROW3_K), U1.32 (CS3)
D1_CS4: DS1.9 (ROW4_K), U1.1 (CS4)
D1_CS5: DS1.4 (ROW5_K), U1.2 (CS5)
D1_CS6: DS1.5 (ROW6_K), U1.3 (CS6)
D1_CS7: DS1.6 (ROW7_K), U1.4 (CS7)
D1_CS8: DS2.12 (ROW1_K), U1.5 (CS8)
D1_CS9: DS2.11 (ROW2_K), U1.6 (CS9)
D1_CS10: DS2.2 (ROW3_K), U1.7 (CS10)
D1_CS11: DS2.9 (ROW4_K), U1.8 (CS11)
D1_CS12: DS2.4 (ROW5_K), U1.10 (CS12)
D1_CS13: DS2.5 (ROW6_K), U1.11 (CS13)
D1_CS14: DS2.6 (ROW7_K), U1.12 (CS14)
D1_SW1: DS1.1 (COL1_A), DS2.1 (COL1_A), U1.22 (SW1)
D1_SW2: DS1.3 (COL2_A), DS2.3 (COL2_A), U1.21 (SW2)
D1_SW3: DS1.10 (COL3_A), DS2.10 (COL3_A), U1.20 (SW3)
D1_SW4: DS1.7 (COL4_A), DS2.7 (COL4_A), U1.19 (SW4)
D1_SW5: DS1.8 (COL5_A), DS2.8 (COL5_A), U1.18 (SW5)
D2_CS1: DS3.12 (ROW1_K), U2.30 (CS1)
D2_CS2: DS3.11 (ROW2_K), U2.31 (CS2)
D2_CS3: DS3.2 (ROW3_K), U2.32 (CS3)
D2_CS4: DS3.9 (ROW4_K), U2.1 (CS4)
D2_CS5: DS3.4 (ROW5_K), U2.2 (CS5)
D2_CS6: DS3.5 (ROW6_K), U2.3 (CS6)
D2_CS7: DS3.6 (ROW7_K), U2.4 (CS7)
D2_CS8: DS4.12 (ROW1_K), U2.5 (CS8)
D2_CS9: DS4.11 (ROW2_K), U2.6 (CS9)
D2_CS10: DS4.2 (ROW3_K), U2.7 (CS10)
D2_CS11: DS4.9 (ROW4_K), U2.8 (CS11)
D2_CS12: DS4.4 (ROW5_K), U2.10 (CS12)
D2_CS13: DS4.5 (ROW6_K), U2.11 (CS13)
D2_CS14: DS4.6 (ROW7_K), U2.12 (CS14)
D2_SW1: DS3.1 (COL1_A), DS4.1 (COL1_A), U2.22 (SW1)
D2_SW2: DS3.3 (COL2_A), DS4.3 (COL2_A), U2.21 (SW2)
D2_SW3: DS3.10 (COL3_A), DS4.10 (COL3_A), U2.20 (SW3)
D2_SW4: DS3.7 (COL4_A), DS4.7 (COL4_A), U2.19 (SW4)
D2_SW5: DS3.8 (COL5_A), DS4.8 (COL5_A), U2.18 (SW5)
D3_CS1: DS5.12 (ROW1_K), U3.30 (CS1)
D3_CS2: DS5.11 (ROW2_K), U3.31 (CS2)
D3_CS3: DS5.2 (ROW3_K), U3.32 (CS3)
D3_CS4: DS5.9 (ROW4_K), U3.1 (CS4)
D3_CS5: DS5.4 (ROW5_K), U3.2 (CS5)
D3_CS6: DS5.5 (ROW6_K), U3.3 (CS6)
D3_CS7: DS5.6 (ROW7_K), U3.4 (CS7)
D3_CS8: DS6.12 (ROW1_K), U3.5 (CS8)
D3_CS9: DS6.11 (ROW2_K), U3.6 (CS9)
D3_CS10: DS6.2 (ROW3_K), U3.7 (CS10)
D3_CS11: DS6.9 (ROW4_K), U3.8 (CS11)
D3_CS12: DS6.4 (ROW5_K), U3.10 (CS12)
D3_CS13: DS6.5 (ROW6_K), U3.11 (CS13)
D3_CS14: DS6.6 (ROW7_K), U3.12 (CS14)
D3_SW1: DS5.1 (COL1_A), DS6.1 (COL1_A), U3.22 (SW1)
D3_SW2: DS5.3 (COL2_A), DS6.3 (COL2_A), U3.21 (SW2)
D3_SW3: DS5.10 (COL3_A), DS6.10 (COL3_A), U3.20 (SW3)
D3_SW4: DS5.7 (COL4_A), DS6.7 (COL4_A), U3.19 (SW4)
D3_SW5: DS5.8 (COL5_A), DS6.8 (COL5_A), U3.18 (SW5)
D4_CS1: DS7.12 (ROW1_K), U4.30 (CS1)
D4_CS2: DS7.11 (ROW2_K), U4.31 (CS2)
D4_CS3: DS7.2 (ROW3_K), U4.32 (CS3)
D4_CS4: DS7.9 (ROW4_K), U4.1 (CS4)
D4_CS5: DS7.4 (ROW5_K), U4.2 (CS5)
D4_CS6: DS7.5 (ROW6_K), U4.3 (CS6)
D4_CS7: DS7.6 (ROW7_K), U4.4 (CS7)
D4_SW1: DS7.1 (COL1_A), U4.22 (SW1)
D4_SW2: DS7.3 (COL2_A), U4.21 (SW2)
D4_SW3: DS7.10 (COL3_A), U4.20 (SW3)
D4_SW4: DS7.7 (COL4_A), U4.19 (SW4)
D4_SW5: DS7.8 (COL5_A), U4.18 (SW5)
GND: C1.2, C2.2, C3.2, C4.2, C5.2, C6.2, C7.2, C8.2, C9.2, C10.2, C11.2, C12.2, C13.2, J1.4, J1.MP, R1.2, R2.2, R3.2, R4.2, R7.2, R9.2, R11.2, R13.2, SW2.2, TP1.1, U1.9 (GND), U1.24 (GND), U1.28 (AD), U1.33 (EP_GND), U2.9 (GND), U2.24 (GND), U2.33 (EP_GND), U3.9 (GND), U3.24 (GND), U3.33 (EP_GND), U4.9 (GND), U4.24 (GND), U4.33 (EP_GND), U5.5 (VSS_VSSA), U5.33 (EP_GND), U6.2 (GND)
ISET1: R1.1, U1.25 (ISET)
ISET2: R2.1, U2.25 (ISET)
ISET3: R3.1, U3.25 (ISET)
ISET4: R4.1, U4.25 (ISET)
LED_SDB: R7.1, U1.29 (SDB), U2.29 (SDB), U3.29 (SDB), U4.29 (SDB), U5.15 (PB0_LED_SDB)
NRST: C12.1, R8.1, SW2.1, TP5.1, U5.6 (PF2_NRST)
SCL: R5.2, U1.27 (SCL), U2.27 (SCL), U2.28 (AD), U3.27 (SCL), U4.27 (SCL), U5.30 (PB6_I2C1_SCL)
SDA: R6.2, U1.26 (SDA), U2.26 (SDA), U3.26 (SDA), U3.28 (AD), U4.26 (SDA), U5.31 (PB7_I2C1_SDA)
SWDIO: TP3.1, U5.24 (PA13_SWDIO)
USB_DM: J1.2, U5.22 (PA11_USB_DM)
USB_DP: J1.3, U5.23 (PA12_USB_DP)
VBUS: F1.1, J1.1

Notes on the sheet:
BANK 1 / modules 1 + 2 / address 0x34
BANK 2 / modules 3 + 4 / address 0x35
BANK 3 / modules 5 + 6 / address 0x36
BANK 4 / module 7 / address 0x37
CONTROLLER / USB, artwork and recovery
POWER / protected input and 3V3 regulator
BUS PULL-UPS / shutdown default / CC current-advertisement sensing
SWD RECOVERY / test contacts
Named nets connect all matching labels on this sheet. Every physical package pin is shown; crosses mark intentional no-connects.
47k ISET limits LED pulse current. LED_SDB defaults low. Firmware must authorise USB current before bright playback. USB data and recovery share the carrier harness.

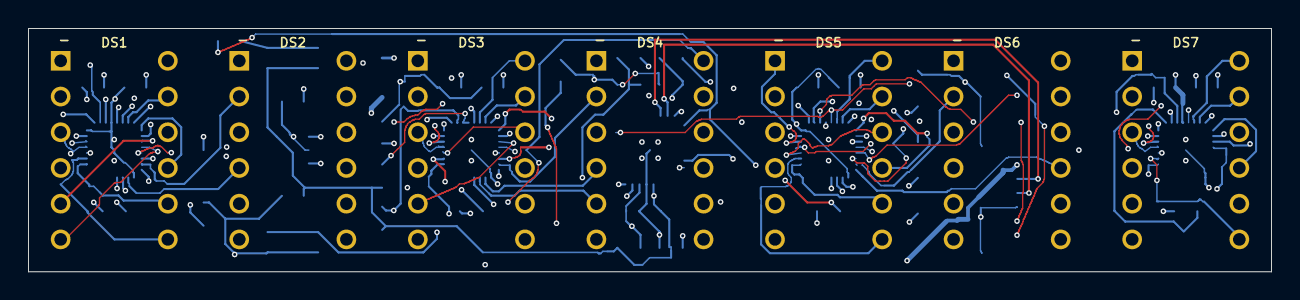
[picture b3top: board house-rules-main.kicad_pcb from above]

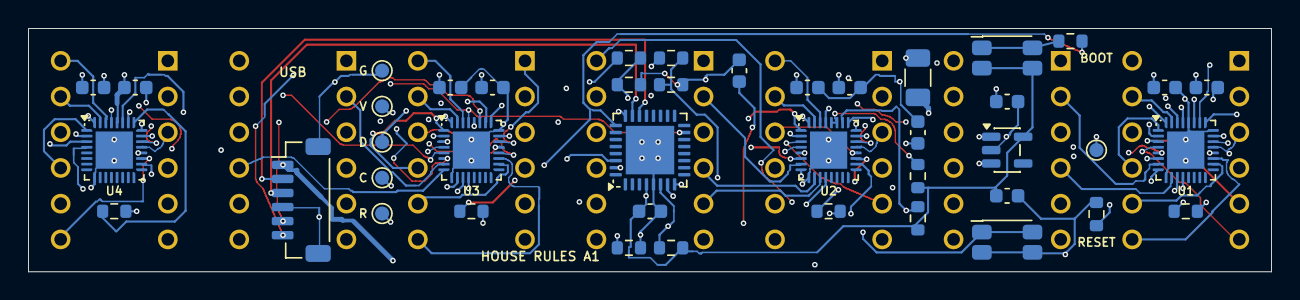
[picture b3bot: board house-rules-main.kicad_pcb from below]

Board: 6 copper layers, 88.4 x 17.3 mm, 50 parts (43 on the bottom side), 90 nets.

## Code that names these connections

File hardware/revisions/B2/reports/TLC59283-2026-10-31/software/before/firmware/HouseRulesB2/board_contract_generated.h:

// Generated from scan-map.json; do not edit this header.
#pragma once
#include "scan_engine.h"
namespace hrb2 {
static constexpr Layout kBoardLayout = {{0,1,2,3,4,5,6,7,8,9,10,11,12,13,16,17,18,19,20,21,22,23,24,25,26,27,28,29,32,33,34,35,36,37,38,39,40,41,42,43,44,45,48,49,50,51,52,53,54},{55,56,57,58,59}};
static constexpr uint8_t PIN_SIN = 3;
static constexpr uint8_t PIN_SCLK = 2;
static constexpr uint8_t PIN_LAT = 4;
static constexpr uint8_t PIN_BLANK = 28;
static constexpr uint8_t PIN_DRIVER_ENABLE = 6;
static constexpr uint8_t PIN_CC1_ADC = 26;
static constexpr uint8_t PIN_CC2_ADC = 27;
static constexpr uint8_t PIN_BC_DET = 7;
static constexpr uint8_t PIN_BC_AL_N = 0;
static constexpr uint32_t RAIL_SETTLE_US = 10000;
static constexpr const char *CONTRACT_SHA256 = "39d47ccdf963ff9bad61d2c7c43dda75683a82660b242edb64cbccaee1a05536";
}

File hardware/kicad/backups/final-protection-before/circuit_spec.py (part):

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        nrows=14 if d<4 else 7
        pins.update({p:f'D{d}_CS{i+1}' for i,p in enumerate(cs_pins[:nrows])})
        pins.update({p:f'D{d}_SW{i+1}' for i,p in enumerate(sw_pins[:5])})
        pins.update({9:'GND',24:'GND',33:'GND',23:'+5V',25:f'ISET{d}',26:'SDA',27:'SCL',28:['GND','SCL','SDA','+5V'][d-1],29:'LED_SDB'})
        names={p:f'CS{i+1}' for i,p in enumerate(cs_pins)}
        names.update({p:f'SW{i+1}' for i,p in enumerate(sw_pins)})
        names.update({9:'GND',24:'GND',33:'EP_GND',23:'VCC',25:'ISET',26:'SDA',27:'SCL',28:'AD',29:'SDB'})
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    passive('main','R12','47k 1%','CC2','CC2_ADC',45.7,2.1)
    passive('main','R13','47k 1%','CC2_ADC','GND',45.7,4.0)
    passive('main','F1','750mA PPTC','VBUS','+5V',25.15,3.5,90,fp='Fuse:Fuse_1206_3216Metric',mpn='SMD1206B075TF/16',lcsc='C269118',role='Fault protection, not USB current authorisation')
    for ref,y,a,b,label in [('SW1',2.1,'BOOT_SWCLK','+3V3','BOOT'),('SW2',15.2,'NRST','GND','RESET')]:
        part('main',ref,label,'Button_Switch_SMD:SW_SPST_EVQP7A',18.8,y,{1:a,2:b},mpn='EVQP7A01P')
    harness={1:'VBUS',2:'USB_DM',3:'USB_DP',4:'GND',5:'CC1',6:'CC2','MP':'GND'}
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    # Junction pad numbers for USB4105 should always be audited against actual footprint.
    result={'revision':'A1','status':'engineering prototype; physical pin test and bench validation required',
            'boards':{'main':{'width':88.4,'height':17.3,'layers':6,'thickness':1.6},'usb':{'width':16.0,'height':16.8,'layers':4,'thickness':1.0}},'parts':PARTS,
            'harness':{'length_mm':'30-50','pin_order':['VBUS','USB_DM','USB_DP','GND','CC1','CC2'],'rule':'Pin1 to pin1 by number at both ends; verify before connection; keep data pair together'}}
    OUT.mkdir(parents=True,exist_ok=True)
    (OUT/'circuit-spec.json').write_text(json.dumps(result,indent=2)+'\n')
    return result
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
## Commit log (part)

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2025-10-18 add original images of the artwork
2025-10-18 improve code
2025-10-18 added web app version
2025-10-18 Add web app link to README
    Added link to the web app in the README.
2025-10-18 remove randomiser and add complete "rules" list
2025-10-18 update: add full "rules" list to website
2025-10-18 feat: add real expressive words
2025-10-20 updated words list
2025-10-20 update: better data structures and logic
2025-10-20 update: make it easier to get exact size of sign in a window
2025-10-20 fix: change how scaling factor is used
2025-10-20 update: try new ppi fetching method
2025-10-20 update: ppi stuff now works with macos
2025-10-20 update: might work on both now
2025-10-20 cleanup: remove old clunky code
2025-10-20 update: move data to json
2025-10-20 fix: didnt like aspect ratio resizing
2025-10-21 fix: make gap work properly
2025-10-21 update: add perfect looping
2025-10-21 update: complete redo of web app
2026-02-20 move index.html for github pages
2026-02-20 Remove web app link from README
2026-02-20 Add link to web app in README
